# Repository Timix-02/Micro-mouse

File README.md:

# Micro-mouse
The micro-mouse project entails the design and implementation of a maze-solving robot, [Veritasium video](https://www.youtube.com/watch?v=ZMQbHMgK2rw). The design will concentrate on the hardware design, supplemented by minor software components, within a strict budgetary framework. Project components are subdivided into four modules: processor, motherboard, sensing, and power. While the motherboard and processor modules are pre-designed, the focus lies on developing the sensor and power modules.

The power module is tasked with the holistic power supply of the system, encompassing motor functionality and battery charging. Design considerations necessitate compatibility with motherboard pin headers and an appropriate form factor for integration with the robot.

Conversely, the sensor module is responsible for object detection/sensing. It must seamlessly integrate with motherboard pin headers and align with robot size specifications.

Successful project completion hinges upon a comprehensive understanding of the module's role within the overall system architecture, coupled with meticulous adherence to specified requirements. Group members assume responsibility for either the power or sensing subsystem. 

PCB manufacturing is done by JLPCB, thus components are limited to their inventory.

## Sensing Subsytem
The sensor PCB functions as the "eyes" of the robot, providing crucial obstacle detection information to the processor. Key objectives for this submodule include:

1. Detecting obstacles in front of and possibly on the sides of the robot.
2. Implementing switching mechanisms to conserve power during idle periods.
3. Ensuring system reliability through rigorous testing and validation.
4. Managing power consumption to avoid premature battery depletion.
5. Developing code to interface the sensor with the processor, demonstrating effective wall detection.

The sensor board must align with the 2x14 connection standard and be appropriately sized for integration with the robot. Pin assignments for the sensor board's connection to the motherboard are provided, indicating the associated functions and their respective pin numbers.

Successful completion of the sensor subsystem necessitates a comprehensive understanding of its role within the overall system architecture, coupled with meticulous adherence to specified requirements. This includes ensuring seamless integration with other subsystems and addressing power management challenges to maintain overall system efficiency.

## Power Subsystem
This subsytem of the micro-mouse project is essential as provides power to the entire system. Outlined below are the requirements for this submodule:

1. Operate and run two motors.
2. Relay battery voltage information using an analog connection.
3. Charge the battery
4. Implement power management by means of an ON/OFF switch.

The power module must include a JST PH pin connector for a 1S1P battery as well as a 2x8 connector protruding from the power board with the associated pin assignments connected to the motherboard. 

The power subsystem's PBC design should be compact to minimize the maximum distance of the robot from the center of rotation. This optimization is crucial for enhancing the robot's maneuverability and overall movement efficiency.

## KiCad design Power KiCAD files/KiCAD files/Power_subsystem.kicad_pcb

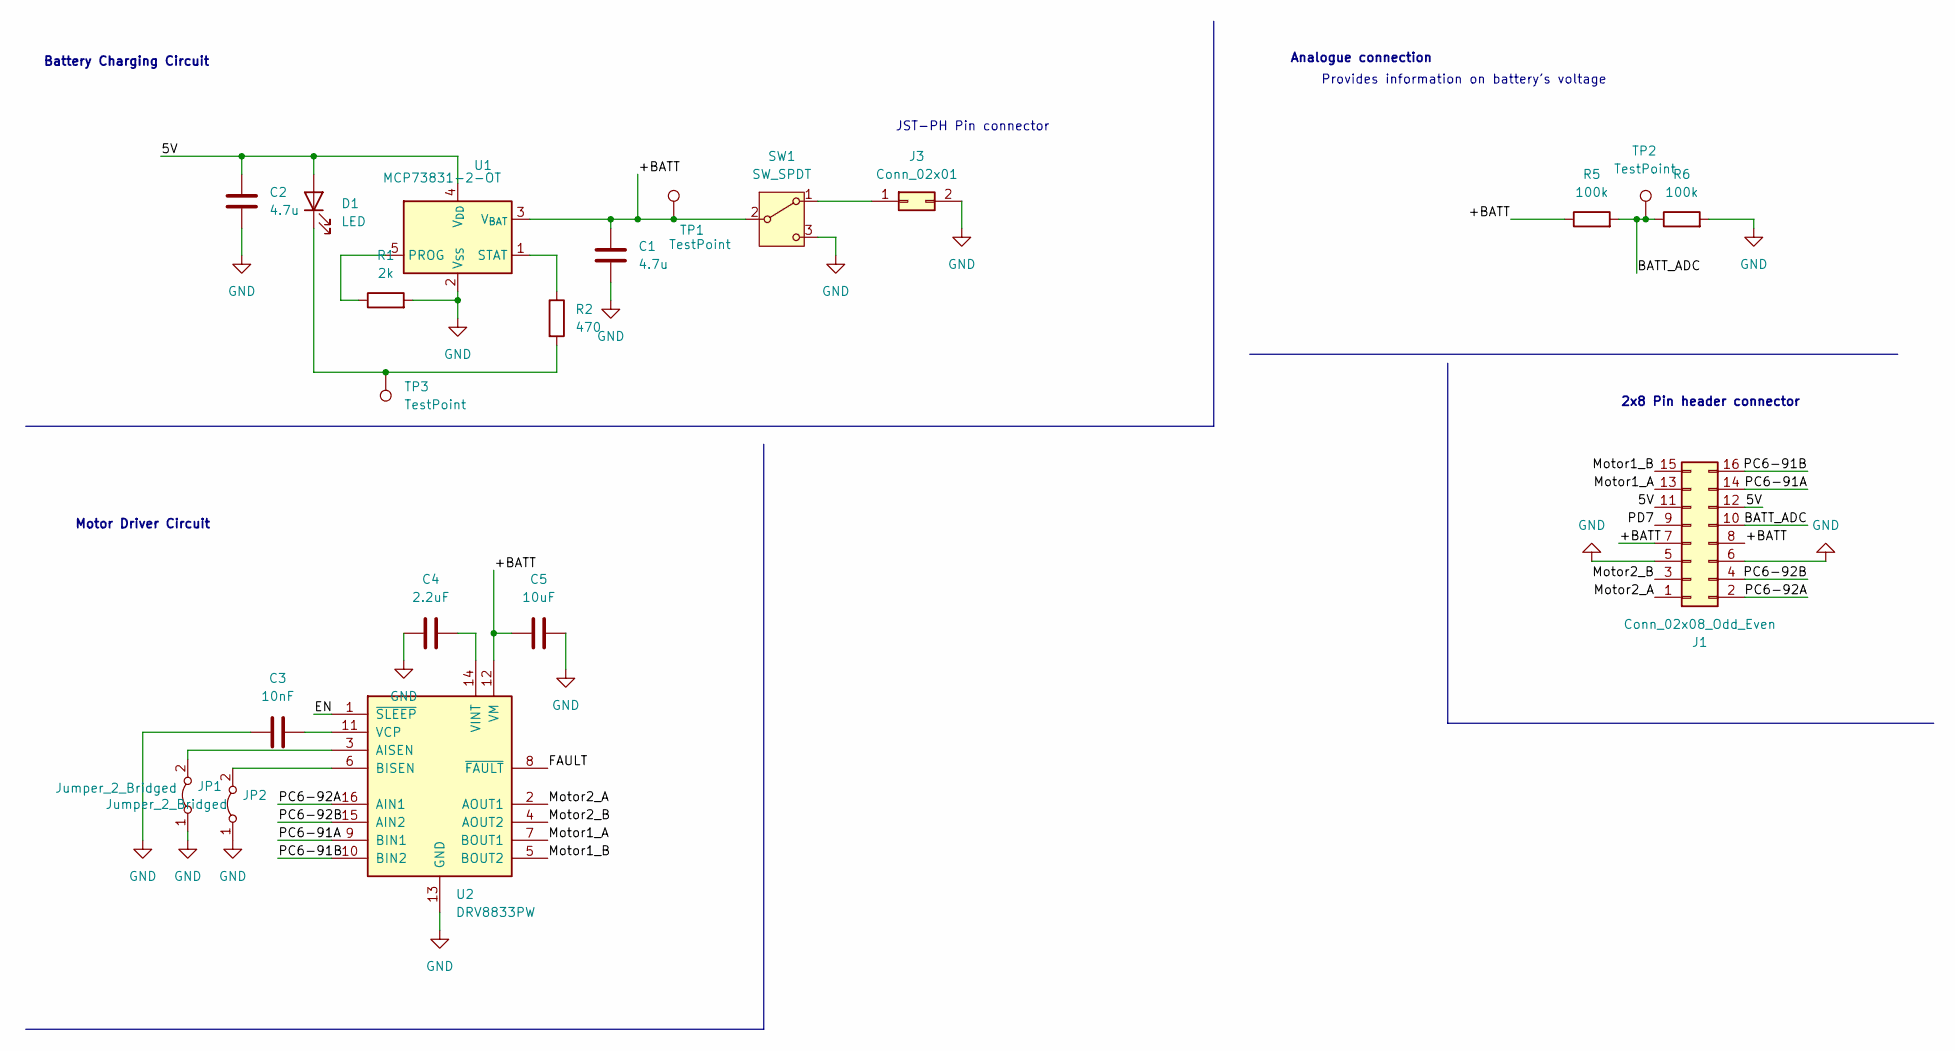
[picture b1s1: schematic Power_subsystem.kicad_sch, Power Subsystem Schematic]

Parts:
C1, C2: 4.7u; C_0805_2012Metric; LCSC C1779
C3: 10nF; C_0805_2012Metric; LCSC C1710
C4: 2.2uF; C_0805_2012Metric; LCSC C377773
C5: 10uF; C_0805_2012Metric; LCSC C15850
D1: LED; LED_0805_2012Metric_Pad1.15x1.40mm_HandSolder; LCSC C2297
J1: Conn_02x08_Odd_Even; PinHeader_2x08_P2.54mm_Vertical
J3: Conn_02x01; JST_PH_B2B-PH-K_1x02_P2.00mm_Vertical
JP1, JP2: Jumper_2_Bridged; SolderJumper-2_P1.3mm_Bridged_RoundedPad1.0x1.5mm
R1: 2k; R_0805_2012Metric; LCSC C17604
R2: 470; R_0805_2012Metric; LCSC C17710
R5, R6: 100k; R_0805_2012Metric; LCSC C149504
SW1: SW_SPDT; SW_Slide-03_Wuerth-WS-SLTV_10x2.5x6.4_P2.54mm
TP1, TP2, TP3: TestPoint; TestPoint_Pad_1.0x1.0mm
U1: MCP73831-2-OT; SOT-23-5; LCSC C424093
U2: DRV8833PW; TSSOP-16-1EP_4.4x5mm_P0.65mm_EP3x3mm; LCSC C50506

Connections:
/5V: C2.1, D1.2 (A), J1.11, J1.12, U1.4 (V_{DD})
/+BATT: C1.1, C5.1, J1.7, J1.8, R5.1, SW1.2 (B), TP1.1, U1.3 (V_{BAT}), U2.12 (VM)
/BATT_ADC: J1.10, R5.2, R6.1, TP2.1
/EN: U2.1 (~SLEEP)
/FAULT: U2.8 (~FAULT)
/Motor1_A: J1.13, U2.7 (BOUT1)
/Motor1_B: J1.15, U2.5 (BOUT2)
/Motor2_A: J1.1, U2.2 (AOUT1)
/Motor2_B: J1.3, U2.4 (AOUT2)
/PC6-91A: J1.14, U2.9 (BIN1)
/PC6-91B: J1.16, U2.10 (BIN2)
/PC6-92A: J1.2, U2.16 (AIN1)
/PC6-92B: J1.4, U2.15 (AIN2)
/PD7: J1.9
GND: C1.2, C2.2, C3.1, C4.1, C5.2, J1.5, J1.6, J3.2, JP1.1 (A), JP2.1 (A), R1.2, R6.2, SW1.3 (C), U1.2 (V_{SS}), U2.13 (GND)
unnamed: D1.1 (K), R2.2, TP3.1
unnamed: J3.1, SW1.1 (A)
unnamed: JP1.2 (B), U2.3 (AISEN)
unnamed: JP2.2 (B), U2.6 (BISEN)
unnamed: R1.1, U1.5 (PROG)
unnamed: R2.1, U1.1 (STAT)
unnamed: C3.2, U2.11 (VCP)
unnamed: C4.2, U2.14 (VINT)

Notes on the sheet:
Battery Charging Circuit
2x8 Pin header connector
Analogue connection
JST-PH Pin connector
Motor Driver Circuit
Provides information on battery's voltage

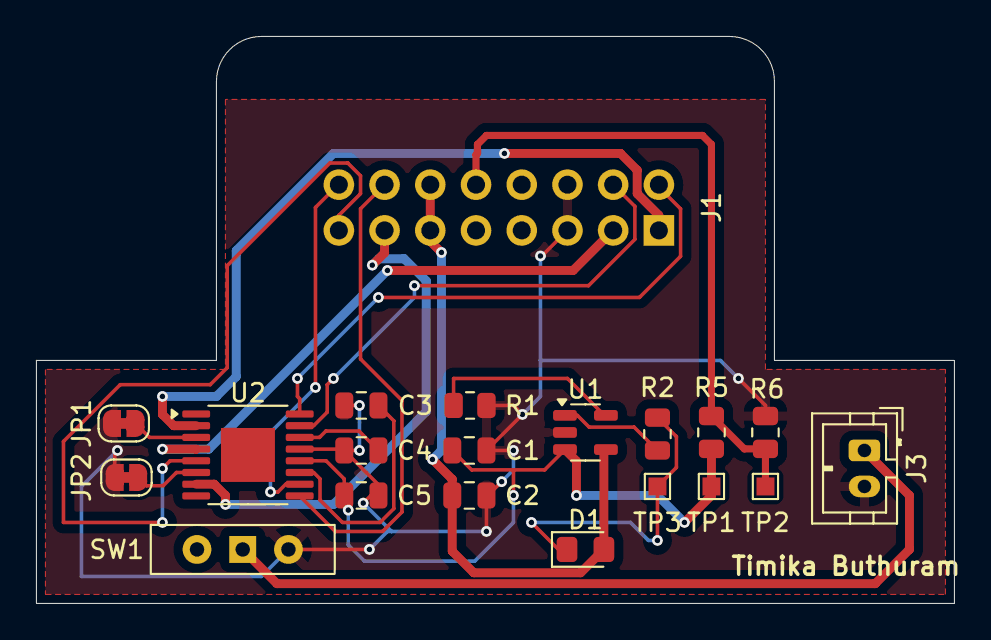
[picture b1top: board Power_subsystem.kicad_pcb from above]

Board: 2 copper layers, 51.0 x 31.5 mm, 20 parts (1 on the bottom side), 20 nets.

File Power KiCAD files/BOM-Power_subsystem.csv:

Comment,Designator,Footprint,LCSC
100k,"R5,R6",R_0805_2012Metric,C149504
10uF,C5,C_0805_2012Metric,C15850
10nF,C3,C_0805_2012Metric,C1710
2k,R1,R_0805_2012Metric,C17604
470,R2,R_0805_2012Metric,C17710
4.7u,"C1,C2",C_0805_2012Metric,C1779
LED,D1,LED_0805_2012Metric_Pad1.15x1.40mm_HandSolder,C2297
2.2uF,C4,C_0805_2012Metric,C377773
MCP73831-2-OT,U1,SOT-23-5,C424093
DRV8833PW,U2,TSSOP-16-1EP_4.4x5mm_P0.65mm_EP3x3mm,C50506

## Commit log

2024-03-24 Update README.md
    project description, test.
2024-03-24 micro-controller datasheet
    file upload test
2024-03-24 Create first file
2024-03-24 Add files via upload
    Datasheets for components used
2024-03-24 Create KiCAD
2024-04-13 Create placeholder
2024-04-21 Update KiCAD
